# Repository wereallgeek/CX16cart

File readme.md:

# CX16-HALF-CART
## CX-16 and OtterX half-sized flash cartridge with EEPROM

### Purpose

This is my interpretation of a simple cartridge for the X16 architecture.
It is intended as a simple cart meant to be programmed within the X16 environment and has minimal components to achieve this goal.

#### History
The OtterX is an X16 clone that is fully compatible with the X16 architecture.

After I completed [construction of the computer the open-source way](https://wereallgeeks.wordpress.com/2026/09/17/completeotterx/), I looked around and didn't initially find an open-source cartridge solution; which is why I cam up with my own.
To achieve this goal, I found a great lot of information on the [git of jkominek](https://github.com/jkominek) - he has a very useful [X16 expansion port & cartridge component/footprint library for KiCad 8](https://github.com/jkominek/x16expansion) that I imported in kicad 10; he also has the [basic design for a simple cartridge](https://github.com/jkominek/x16simplecart) in PDF format, a great head start to design my X16 cartridge.

I started from that and designed the PCB in surface mount with the idea of being able to purchase a lot of PCBs pre-assembled using PCBA services.

I altered the footprint and routed the board by hand, keeping it 2-layer. I think I like the end result.

Altough not tester yet, the layout of the PCB should fit on a standard famicom cartridge shell.

Disclaimer - After spending much time designing my own cart, I was pointed to [this open-source cartridge](https://gitlab.com/m00dawg/commander-x16-cartridges) from [m00dawg](https://gitlab.com/m00dawg)... who also encouraged and guided in this design along with [Wavicle](https://github.com/jburks) and Morphinejh on the X16 discord - thanks.

### Bill of Material

The hardware included on the PCB is as follow
- SST39SF040-70-4C-NHE
- - The FLASH memory, same type as on the CX16 or OtterX but in PLCC form
- 24LC128-I/P
- - I2C EEPROM to save on cart
- SN74ACT00D
- - NAND gates (SOIC14) to assist with logic
- CD74ACT138M96
- - Address decoder (SOIC16)
- CL21B105KBFNNNE (x2)
- - 1uF Decoupling capacitors
- CL21B104KBCNNNC (x4)
- - 100nF Decoupling capacitors
- RC0805FR-0710KL
- - 10k ohm pull-up resistor to put ROM read-only when JP1 is cut open

### How to burn ROM cart

X16 onboard cards or carts can be burn with the same X16 update utility used to update the VERA board or firmware ROM, the X16-FLASH utility

The software is intended to be part of the [essential SD card](https://github.com/cx16forum/sdcard) software, but can also be [found on git](https://github.com/FlightControl-User/x16-flash)

Cartridge binaries would be saved alongside the software and written directly on the X16 hardware.

### Copyright (C) 2026 Marsupial (wereallgeeks.wordpress.com) 

This PCB Design is free hardware: you can redistribute it and/or modify it under the terms of the GNU General Public License as published by the Free Software Foundation version 3,see [license](https://github.com/wereallgeek/CX16cart?tab=License-1-ov-file), as long as PCB attribution markings and silkscreen remains present on the final product.

Commercial profitability is strictly prohibited

This design is distributed in the hope that it will be useful, but WITHOUT ANY WARRANTY; without even the implied warranty of MERCHANTABILITY or FITNESS FOR A PARTICULAR PURPOSE,  or FUNCTIONALITY. 
See the [License](https://github.com/wereallgeek/CX16cart?tab=License-1-ov-file) for more details.

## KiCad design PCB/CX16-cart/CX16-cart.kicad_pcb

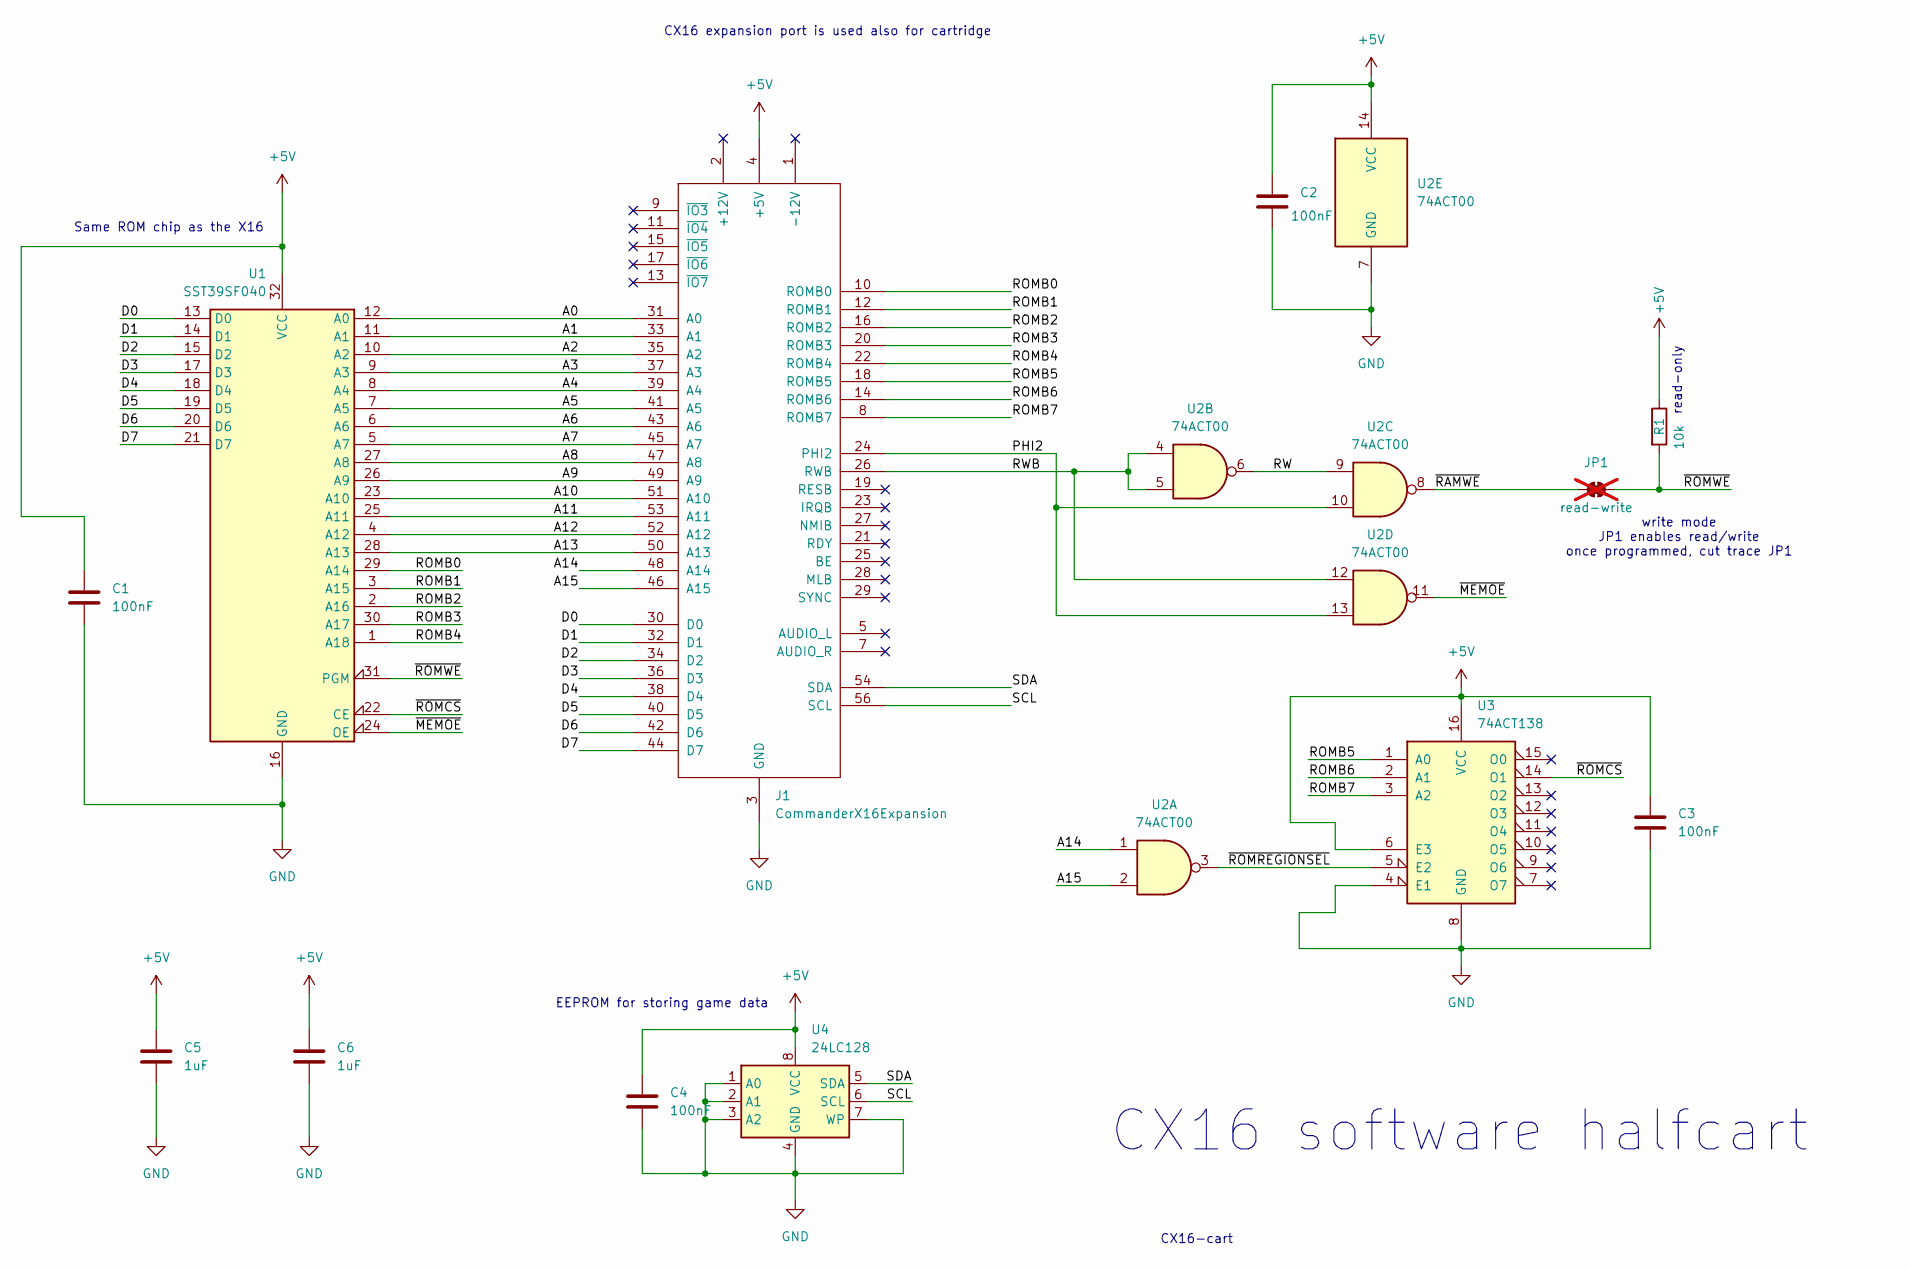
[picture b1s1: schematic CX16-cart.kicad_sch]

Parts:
C1, C2, C3, C4: 100nF; C_0805_2012Metric_Pad1.18x1.45mm_HandSolder; MPN CL21B104KBCNNNC
C5, C6: 1uF; C_0805_2012Metric_Pad1.18x1.45mm_HandSolder; MPN CL21B105KBFNNNE
J1: CommanderX16Expansion; CX16HalfCart
JP1: read-write; Jumper_2_NC_Trace; not fitted
R1: 10k; R_0805_2012Metric_Pad1.20x1.40mm_HandSolder; MPN RC0805FR-0710KL
U1: SST39SF040; PLCC-32_11.4x14.0mm_P1.27mm; MPN SST39SF040-70-4C-NHE
U2: 74ACT00; SOIC-14_3.9x8.7mm_P1.27mm; MPN SN74ACT00D
U3: 74ACT138; SOIC-16_3.9x9.9mm_P1.27mm; MPN CD74ACT138M96
U4: 24LC128; SOIC-8_3.9x4.9mm_P1.27mm; MPN 24LC128-I/SN

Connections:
+5V: C1.1, C2.1, C3.1, C4.1, C5.1, C6.1, J1.4 (+5V), J1.57 (+5V), R1.1, U1.32 (VCC), U2.14 (VCC), U3.6 (E3), U3.16 (VCC), U4.8 (VCC)
/A0: J1.31 (A0), U1.12 (A0)
/A1: J1.33 (A1), U1.11 (A1)
/A2: J1.35 (A2), U1.10 (A2)
/A3: J1.37 (A3), U1.9 (A3)
/A4: J1.39 (A4), U1.8 (A4)
/A5: J1.41 (A5), U1.7 (A5)
/A6: J1.43 (A6), U1.6 (A6)
/A7: J1.45 (A7), U1.5 (A7)
/A8: J1.47 (A8), U1.27 (A8)
/A9: J1.49 (A9), U1.26 (A9)
/A10: J1.51 (A10), U1.23 (A10)
/A11: J1.53 (A11), U1.25 (A11)
/A12: J1.52 (A12), U1.4 (A12)
/A13: J1.50 (A13), U1.28 (A13)
/A14: J1.48 (A14), U2.1
/A15: J1.46 (A15), U2.2
/D0: J1.30 (D0), U1.13 (D0)
/D1: J1.32 (D1), U1.14 (D1)
/D2: J1.34 (D2), U1.15 (D2)
/D3: J1.36 (D3), U1.17 (D3)
/D4: J1.38 (D4), U1.18 (D4)
/D5: J1.40 (D5), U1.19 (D5)
/D6: J1.42 (D6), U1.20 (D6)
/D7: J1.44 (D7), U1.21 (D7)
/PHI2: J1.24 (PHI2), U2.10, U2.13
/ROMB0: J1.10 (ROMB0), U1.29 (A14)
/ROMB1: J1.12 (ROMB1), U1.3 (A15)
/ROMB2: J1.16 (ROMB2), U1.2 (A16)
/ROMB3: J1.20 (ROMB3), U1.30 (A17)
/ROMB4: J1.22 (ROMB4), U1.1 (A18)
/ROMB5: J1.18 (ROMB5), U3.1 (A0)
/ROMB6: J1.14 (ROMB6), U3.2 (A1)
/ROMB7: J1.8 (ROMB7), U3.3 (A2)
/RW: U2.6, U2.9
/RWB: J1.26 (RWB), U2.4, U2.5, U2.12
/SCL: J1.56 (SCL), U4.6 (SCL)
/SDA: J1.54 (SDA), U4.5 (SDA)
/~MEMOE: U1.24 (OE), U2.11
/~RAMWE: JP1.1 (A), U2.8
/~ROMCS: U1.22 (CE), U3.14 (O1)
/~ROMREGIONSEL: U2.3, U3.5 (E2)
/~ROMWE: JP1.2 (B), R1.2, U1.31 (PGM)
GND: C1.2, C2.2, C3.2, C4.2, C5.2, C6.2, J1.3 (GND), J1.6 (GND), J1.55 (GND), J1.58 (GND), U1.16 (GND), U2.7 (GND), U3.4 (E1), U3.8 (GND), U4.1 (A0), U4.2 (A1), U4.3 (A2), U4.4 (GND), U4.7 (WP)

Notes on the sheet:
CX16 expansion port is used also for cartridge
write mode JP1 enables read/write once programmed, cut trace JP1
read-only
EEPROM for storing game data
CX16-cart
CX16 software halfcart
Same ROM chip as the X16

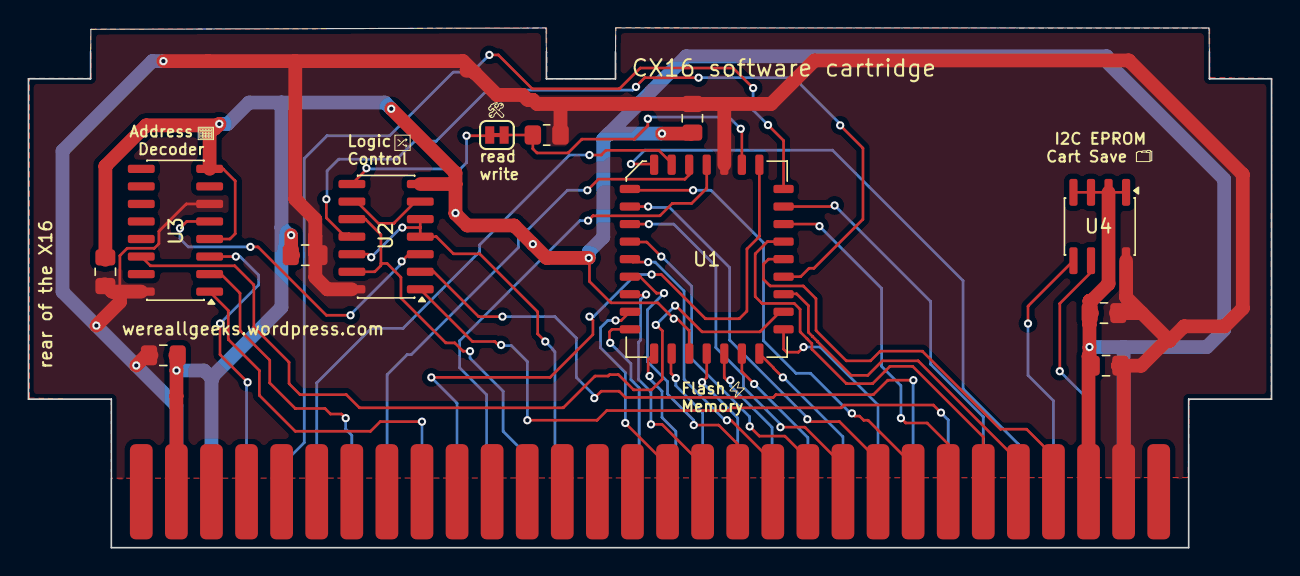
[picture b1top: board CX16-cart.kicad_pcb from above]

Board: 2 copper layers, 90.0 x 37.6 mm, 14 parts (1 on the bottom side), 44 nets.

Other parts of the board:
PixelPanic: LOGO
